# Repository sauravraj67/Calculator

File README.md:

# Calculator

I made a simple Calculator design. The concept is based on Raspberry Pi Pico , It has 19  Mechanical switches directly attached to the raspberry Pi Pico. A rotor encoder whose rotor would be used to change position the position of the cursor and it's button would be used to clean the screen And The Screen would be a 16X2 LCD Display with I2C

## Features
parentheses
decimals
operator precedence
Error Handling
divide by zero
syntax checking
UI Features
boot screen
expression rendering
result rendering
Input Features
matrix scanning
debounce
encoder support
delete key
clear key
Planned Future Features
scientific functions
USB keyboard mode
EEPROM memory
cursor blinking
full LCD drive

## Firmware

The firmware was written in C using the Raspberry Pi Pico SDK.

 ### Schematic<br><br>

###  PCB Design 

### 3D Design <br><br>

# Bill of Materials (BOM)
# Bill of Materials (BOM)

| Index | Quantity | Part Description | Link | Cost |
|---|---:|---|---|---:|
| 1 | 1 | PCB + 3D Printed Case + Shipping | https://jlcpcb.com | $16.2 |
| 2 | 1 | Screws Kit | https://www.amazon.in/gp/product/B0C394FK9B/ref=ewc_pr_img_1?smid=A31OPLJ1CRU4J5&th=1 | $3.87 |
| 3 | 1 | M3 × 6 mm Brass Heat Inserts | https://www.amazon.in/gp/product/B0BB86CQSJ/ref=ewc_pr_img_2?smid=A2JDRZEGU1IDE2&psc=1 | $0.79 |
| 4 | 2 | Keycap Set | https://www.amazon.in/gp/product/B0F13YK4D6/ref=ewc_pr_img_3?smid=AH0KEO6T9U8SH&psc=1 | $9.20 |
| 5 | 1 | Mechanical Keyboard Switches | https://www.amazon.in/gp/product/B0G39H2G4H/ref=ewc_pr_img_4?smid=ANH0PBBCLPM1Q&psc=1 | $5.37 |
| 6 | 1 | Rotary Encoder Module | https://www.amazon.in/gp/product/B0888RWNM1/ref=ewc_pr_img_5?smid=A34QREQHZ8C5B0&psc=1 | $1.84 |
| 7 | 1 | LCD Display Module with I2C Interface | https://www.amazon.in/gp/product/B08THCDP8L/ref=ewc_pr_img_6?smid=AJ6SIZC8YQDZX&psc=1 | $3.87 |
| 8 | 1 | Raspberry Pi Pico | https://www.amazon.in/gp/product/B08WPNM7JB/ref=ewc_pr_img_7?smid=AJ6SIZC8YQDZX&psc=1 | $7.51 |

## Total Cost

**$48.68 USD**

---

## Notes

- Prices may vary depending on region, taxes, shipping, and seller availability so i used 1USD= 93 Inr for conversion.
- PCB fabrication and shipping costs were estimated using JLCPCB.
- The keycap cost is calculated for 2 sets (`$4.60 × 2 = $9.20`).

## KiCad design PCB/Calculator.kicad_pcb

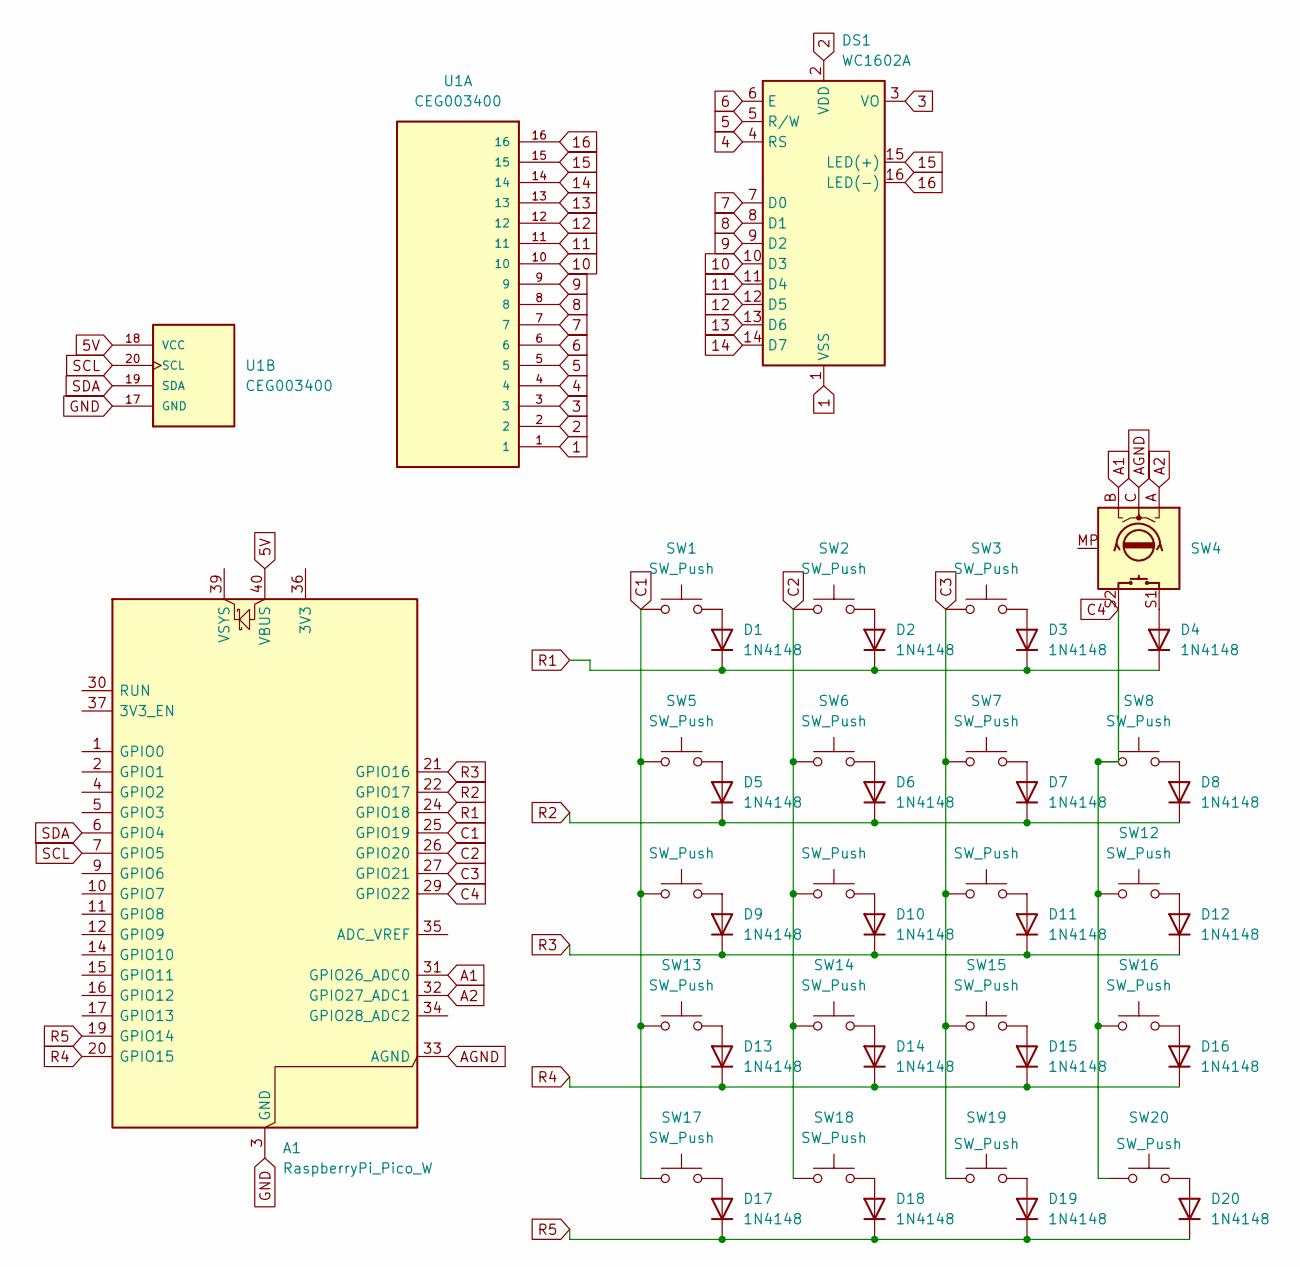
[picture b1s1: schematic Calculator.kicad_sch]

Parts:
A1: RaspberryPi_Pico_W; RaspberryPi_Pico_Common_THT
D1, D2, D3, D4, D5, D6, D7, D8, D9, D10, D11, D12, D13, D14, D15, D16, D17, D18, D19, D20: 1N4148; D_DO-35_SOD27_P7.62mm_Horizontal
DS1: WC1602A
SW1, SW2, SW3, SW5, SW6, SW7, SW8, SW9, SW10, SW11, SW12, SW13, SW14, SW15, SW16, SW17, SW18, SW19, SW20: SW_Push; SW_Cherry_MX_1.00u_PCB
SW4: RotaryEncoder_Switch_MP; RotaryEncoder_Alps_EC11E-Switch_Vertical_H20mm
U1: CEG003400; MODULE_CEG003400; PARTREV N/A

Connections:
1: DS1.1 (VSS), U1.1
2: DS1.2 (VDD), U1.2
3: DS1.3 (VO), U1.3
4: DS1.4 (RS), U1.4
5: DS1.5 (R/W), U1.5
5V: A1.40 (VBUS), U1.18 (VCC)
6: DS1.6 (E), U1.6
7: DS1.7 (D0), U1.7
8: DS1.8 (D1), U1.8
9: DS1.9 (D2), U1.9
10: DS1.10 (D3), U1.10
11: DS1.11 (D4), U1.11
12: DS1.12 (D5), U1.12
13: DS1.13 (D6), U1.13
14: DS1.14 (D7), U1.14
15: DS1.15 (LED(+)), U1.15
16: DS1.16 (LED(-)), U1.16
A1: A1.31 (GPIO26_ADC0), SW4.B
A2: A1.32 (GPIO27_ADC1), SW4.A
AGND: A1.33 (AGND), SW4.C
C1: A1.25 (GPIO19), SW1.1, SW5.1, SW9.1, SW13.1, SW17.1
C2: A1.26 (GPIO20), SW2.1, SW6.1, SW10.1, SW14.1, SW18.1
C3: A1.27 (GPIO21), SW3.1, SW7.1, SW11.1, SW15.1, SW19.1
C4: A1.29 (GPIO22), SW4.S2, SW8.1, SW12.1, SW16.1, SW20.1
GND: A1.3 (GND), A1.8 (GND), A1.13 (GND), A1.18 (GND), A1.23 (GND), A1.28 (GND), A1.38 (GND), U1.17 (GND)
unnamed: D1.2 (A), SW1.2
unnamed: D2.2 (A), SW2.2
unnamed: D3.2 (A), SW3.2
unnamed: D4.2 (A), SW4.S1
unnamed: D5.2 (A), SW5.2
unnamed: D6.2 (A), SW6.2
unnamed: D7.2 (A), SW7.2
unnamed: D8.2 (A), SW8.2
unnamed: D9.2 (A), SW9.2
unnamed: D10.2 (A), SW10.2
unnamed: D11.2 (A), SW11.2
unnamed: D12.2 (A), SW12.2
unnamed: D13.2 (A), SW13.2
unnamed: D14.2 (A), SW14.2
unnamed: D15.2 (A), SW15.2
unnamed: D16.2 (A), SW16.2
unnamed: D17.2 (A), SW17.2
unnamed: D18.2 (A), SW18.2
unnamed: D19.2 (A), SW19.2
unnamed: D20.2 (A), SW20.2
R1: A1.24 (GPIO18), D1.1 (K), D2.1 (K), D3.1 (K), D4.1 (K)
R2: A1.22 (GPIO17), D5.1 (K), D6.1 (K), D7.1 (K), D8.1 (K)
R3: A1.21 (GPIO16), D9.1 (K), D10.1 (K), D11.1 (K), D12.1 (K)
R4: A1.20 (GPIO15), D13.1 (K), D14.1 (K), D15.1 (K), D16.1 (K)
R5: A1.19 (GPIO14), D17.1 (K), D18.1 (K), D19.1 (K), D20.1 (K)
SCL: A1.7 (GPIO5), U1.20 (SCL)
SDA: A1.6 (GPIO4), U1.19 (SDA)

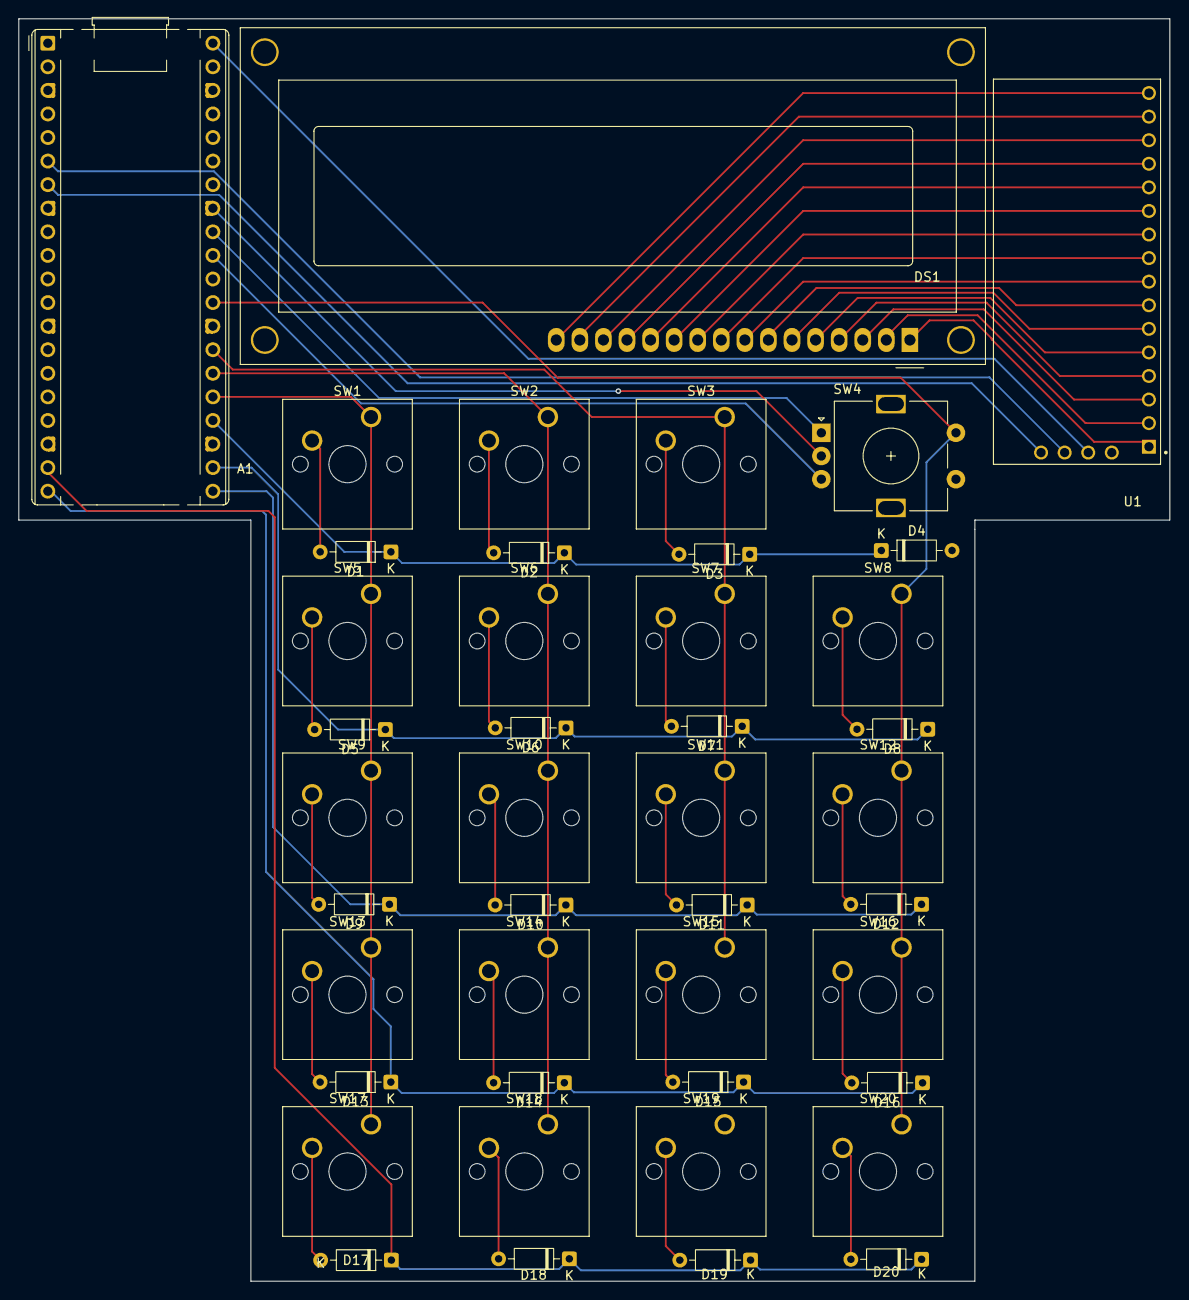
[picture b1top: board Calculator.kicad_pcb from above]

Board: 2 copper layers, 124.0 x 136.0 mm, 43 parts (0 on the bottom side), 52 nets.
